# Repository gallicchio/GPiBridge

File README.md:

# GPiBridge

*By Jason Gallicchio <jason@hmc.edu> and Claude. GPIB with a lowercase i, for the Pi.
Home: [github.com/gallicchio/GPiBridge](https://github.com/gallicchio/GPiBridge).*

**How it was made:** Jason and Claude designed it in a Claude Code conversation, recorded
prompt by prompt in **[CLAUDE_CODE_CHAT.md](CLAUDE_CODE_CHAT.md)**. Claude wrote the
generators that draw the schematic, the board and the housing, the firmware and these
documents; [CLAUDE_PCB.md](CLAUDE_PCB.md) holds the lessons from earlier boards that it
followed.

**An open USB-C to GPIB (IEEE-488) adapter.** It plugs straight into an instrument's
GPIB socket, in a housing the size of a GPIB cable's hood. To the computer it is a
**Prologix-compatible controller**: one USB serial port that speaks the publicly
documented "++" commands, with the drivers built into Linux, macOS and Windows 10/11.
PyVISA-py's Prologix support (`PRLGX-ASRL0::<port>::INTFC`), EZGPIB, KE5FX's tools,
`lab-instrument-control` and scripts written for the Prologix work unchanged, given the
new port name (`HANDBOOK.md` §2). A standard **USB test-and-measurement** (USBTMC/USB488)
personality is planned for a later firmware.

| | |
|---|---|
|  |  |

Inside:
- An **RP2354A** (RP2350 with 2 MB of flash in the package). It runs the bus and USB,
  and takes new firmware over the same USB cable: `picotool` reboots it into its ROM
  bootloader from software, so nobody presses a button.
- **Real IEEE-488 transceivers**, TI's SN75160B (data) and SN75161B (control). They give
  48 mA sinks, the bus terminations and receiver hysteresis, and no load on the bus when
  unpowered. Their 5 V is switched on only after the firmware has every line released
  and the USB host has agreed to the current, so plugging the adapter into a live bus
  cannot disturb it.
- One USB-C receptacle out of the end of a thin board, three LEDs (USB, BUS, ERR), a
  BOOT button behind a pinhole, and two Raspberry Pi debug connectors (SWD and a UART
  console) under openings in the lid.
- **Its own logic analyser.** The RP2354A's second core can record all 16 bus lines
  during a transaction, at 83 ns resolution. The record goes out as a VCD, which
  PulseView decodes as GPIB (`++t capture`).

## GPiBridge Lite

The same adapter without the transceivers, for one instrument (or a few on a short
cable). Its RP2354A's pins meet the bus through 100 R each and drive it open-drain:
low to assert, let go to release, with the pads' output forced low in hardware so no
pin can ever drive a line high. It is the same size, fits the same housing (its own
lid says "Lite"), and runs the same firmware image, which reads which board it is on
at start-up (R21 on DC: 10 k up on GPiBridge, 1 k down on the Lite).

| | GPiBridge | GPiBridge Lite |
|---|---|---|
| bus drivers | SN75160B + SN75161B: 48 mA sinks, terminations, hysteresis | the RP2354A's pins, through 100 R: 12 mA sinks |
| instruments | a full bus | one, or a few on a short cable |
| unpowered (USB unplugged) | no load on the bus (TI's transceivers) | nearly none: the RP2350's pins tolerate 3.63 V unpowered; a standard bus idles at about 3.4 V |
| USB current | up to 270 mA with the drivers active | about 40 mA |
| 5 bare boards, 2 assembled (JLCPCB's quote, 2026-10-06) | $24.80 + $60.56 assembly = $85 | $25.85 + $40.18 assembly = $66 |

`DESIGN_NOTES.md` §7 has the Lite's design and its limits.

**Status: rev A of both boards has been ordered from JLCPCB, assembled, but not yet
received** (2026-10-06: 5 boards of each, 2 of them assembled). Both pass every check
(schematic ERC 0, DRC 0 at every severity with schematic parity); their JLCPCB releases
are in `mfg/release/` and `mfg/release-lite/`, and the housing (one base, a lid for each)
in `enclosure/out/`. The firmware builds and passes its host tests against a simulated
instrument, for both boards' pin layers, and sigrok's own IEEE-488 decoder reads their
simulated bus traffic correctly. Nothing has run on real hardware yet. After the order
JLCPCB ran out of L1 (the Abracon AOTA inductor) and rev A is built with a TDK
VLS201612HBX-3R3M-1 instead, chosen on 2026-10-18 in their Replace Parts dialog; the design
keeps the AOTA (`DESIGN_NOTES.md` risk 8). `BRINGUP.md` is
the plan for the first boards, and the shopping list.

## Using it

```sh
python3 tools/gpibridge.py list            # find it: its "GPiBridge GPIB" port
python3 tools/gpibridge.py idn 10          # *IDN? of the instrument at GPIB address 10
python3 tools/gpibridge.py capture 10 "*IDN?" idn    # the same, with the bus recorded: idn.vcd
```

or any Prologix program, on the "GPiBridge GPIB" port:

```
++addr 10
*IDN?
++read eoi
HEWLETT-PACKARD,33120A,0,7.0-5.0-1.0
```

The commands are the Prologix manual's (controller mode), plus `++t …` extensions
(`++t help`). `docs/PINOUT.md` has the pinout; `HANDBOOK.md` covers use, firmware
updates and recovery.

## The repository

| path | what |
|---|---|
| `PLAN.md` | the decisions and the state of the work |
| `HANDBOOK.md` | bring-up of one board, use on each OS, Prologix compatibility, recovery |
| `BRINGUP.md` | the first boards: what to buy, what plugs where, the test stages, logic analysers |
| `AGENTS.md` | how an LLM (or a person) builds, flashes, tests and debugs it |
| `DESIGN_NOTES.md` | why the design is as it is, and how rev A could fail |
| `gen/` | the generators: parts, symbols, schematic, placement, routing, silkscreen |
| `hardware/` | the KiCad 10 projects they write: `GPiBridge` and `GPiBridgeLite` (schematic, board), one library |
| `mfg/` | the JLCPCB releases (`release/`, `release-lite/`) and their checks |
| `enclosure/` | the two-part housing (FreeCAD Python) for JLC3DP: one base, a lid for each board |
| `firmware/` | Pico SDK + TinyUSB firmware, host tests with a simulated bus |
| `tools/` | checks, renders, the host tool `gpibridge.py` |
| `docs/` | pictures, pinout, schematic PDF |
| [`CLAUDE_CODE_CHAT.md`](CLAUDE_CODE_CHAT.md) | the conversation that designed it, every prompt and response |
| [`CLAUDE_PCB.md`](CLAUDE_PCB.md) | the lessons from earlier boards that it follows (a public snapshot; the working copy is in Jason's private OpticsPCBs repository) |

`python3 build.py` makes everything from the generators, for both boards
(`GPIBRIDGE_VARIANT=lite` selects the Lite in any single generator). Everything a
reviewer or a fab needs is committed, so nothing has to be built to look at the design or
order it.

## Licence

Hardware: CERN-OHL-P-2.0. Software and firmware: MIT. See `LICENSE`. Raspberry Pi's
RP2350 regulator layout and footprints (`gen/rpi_minimal/`) are theirs, MIT licensed.

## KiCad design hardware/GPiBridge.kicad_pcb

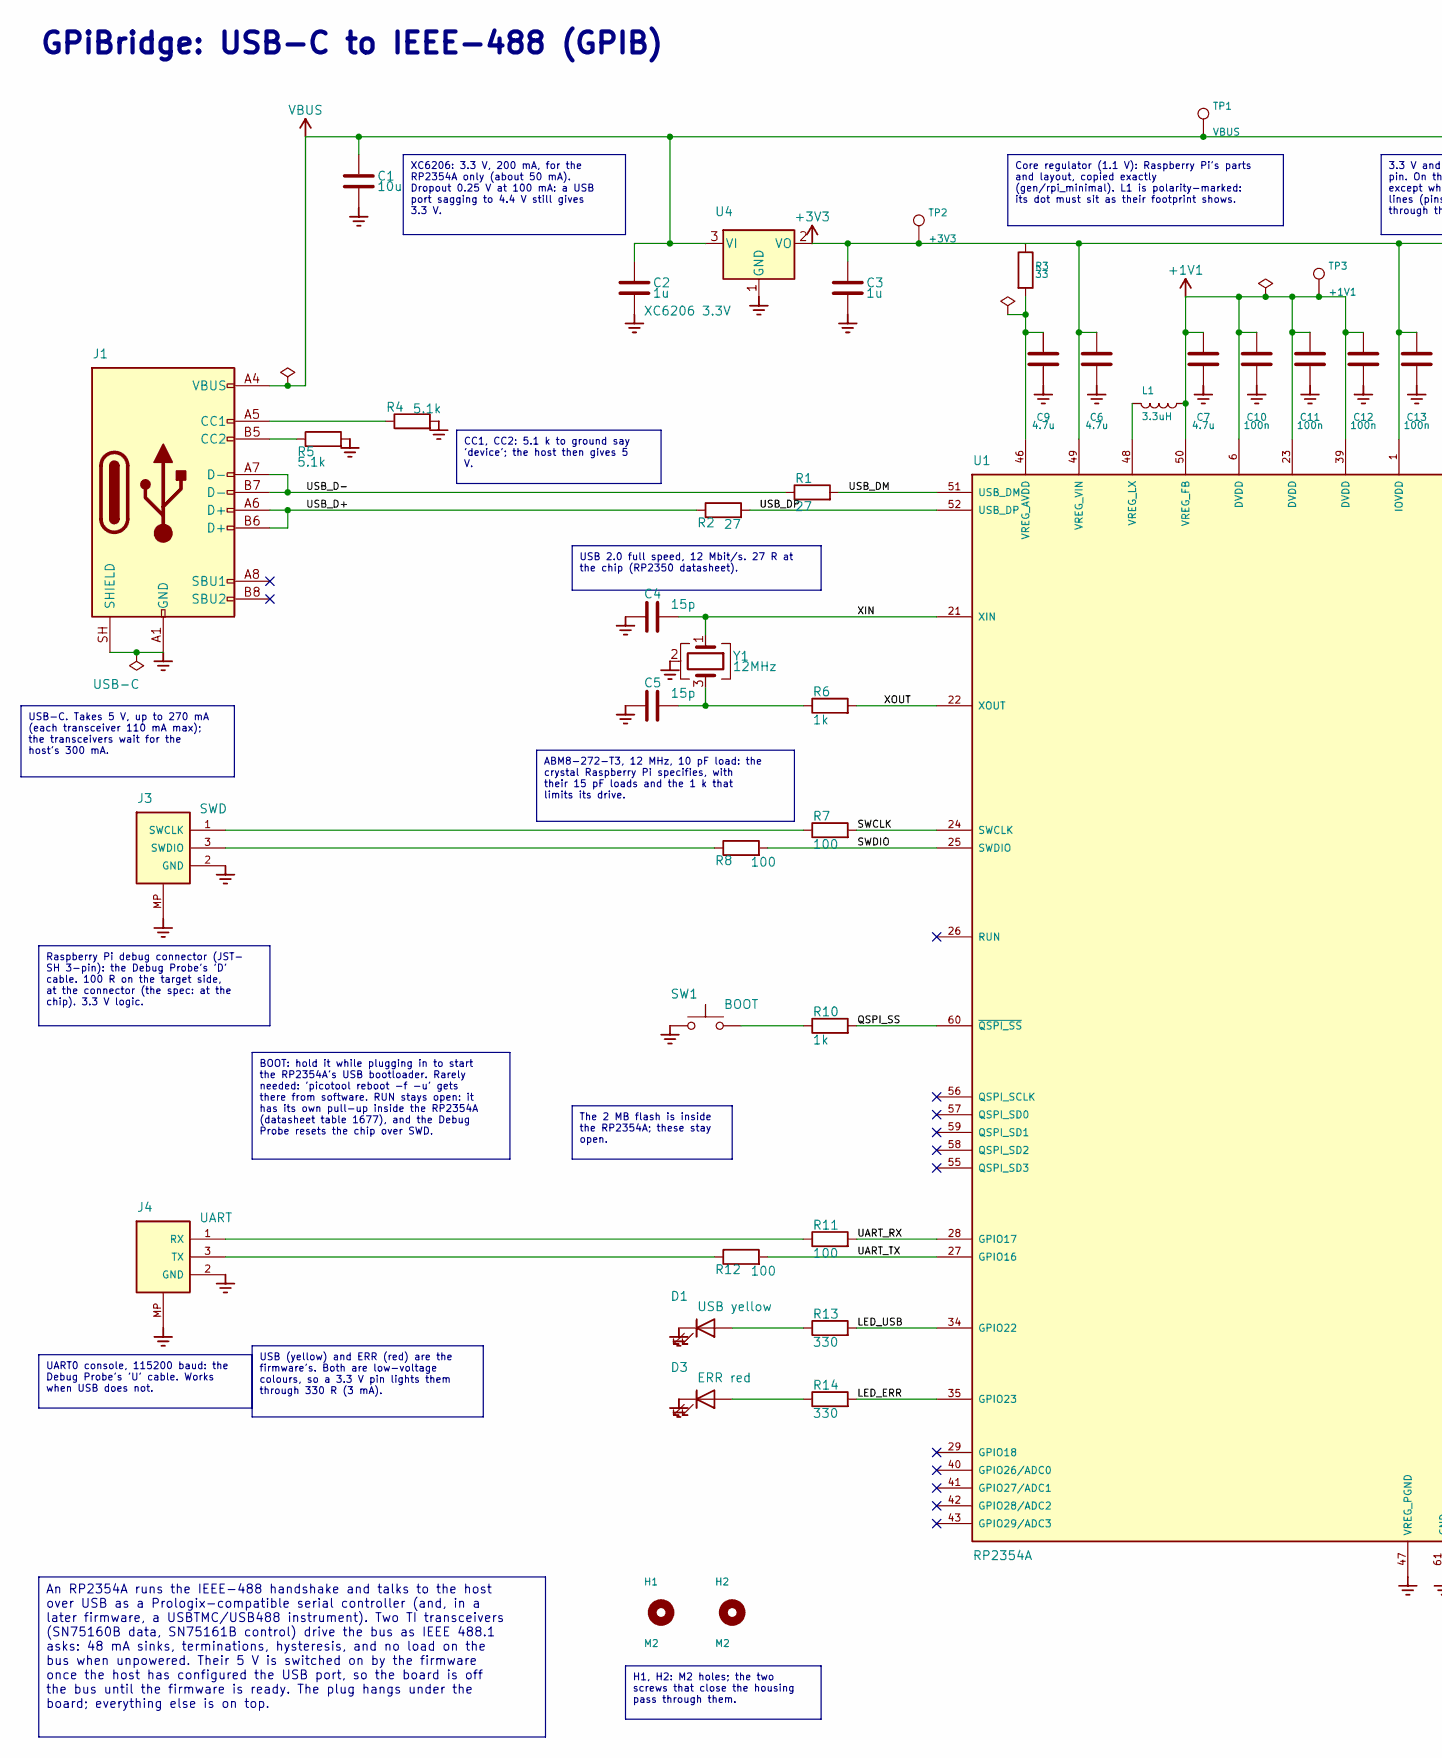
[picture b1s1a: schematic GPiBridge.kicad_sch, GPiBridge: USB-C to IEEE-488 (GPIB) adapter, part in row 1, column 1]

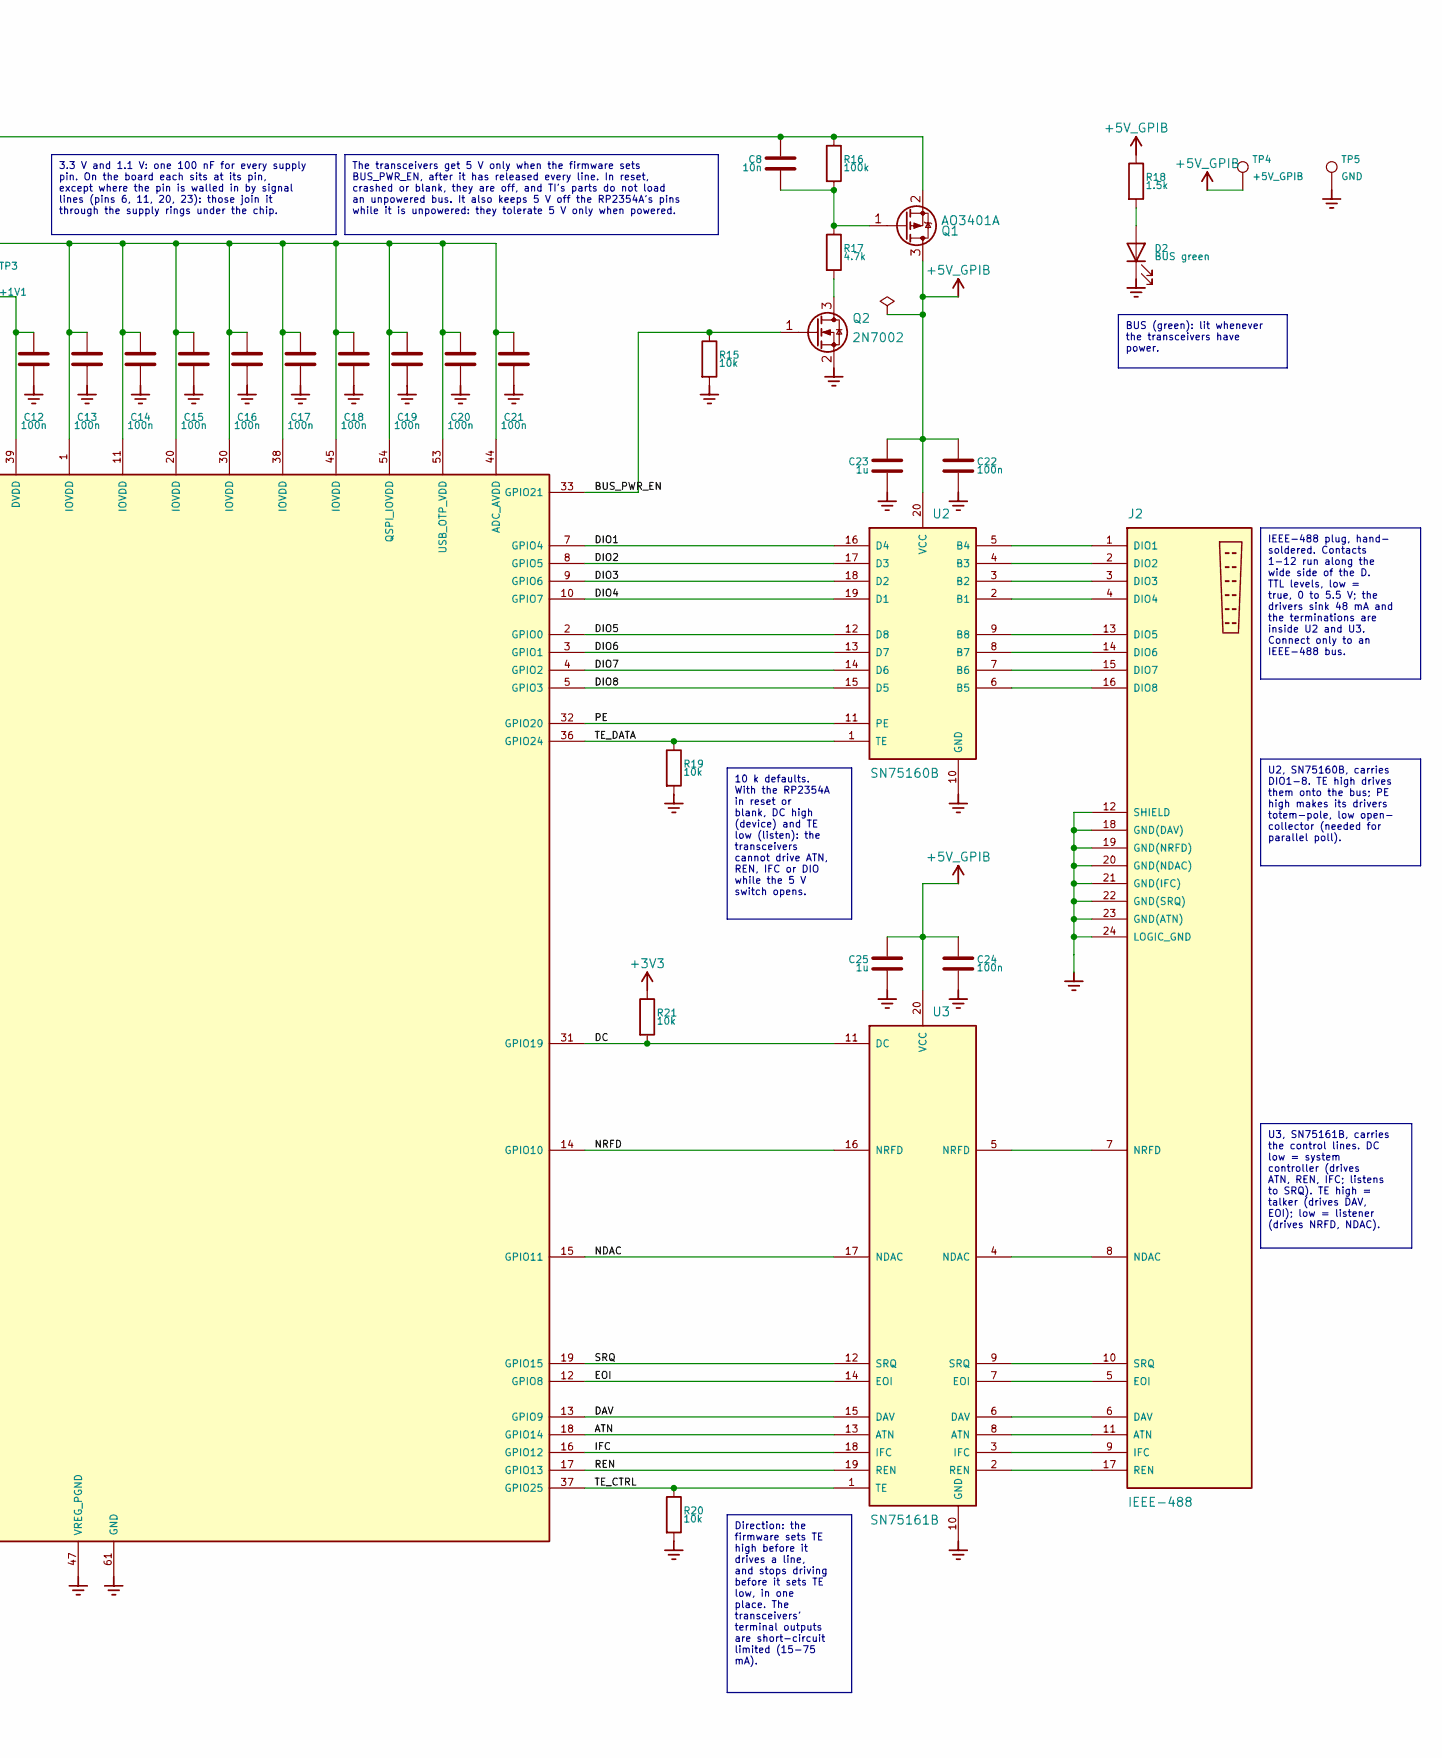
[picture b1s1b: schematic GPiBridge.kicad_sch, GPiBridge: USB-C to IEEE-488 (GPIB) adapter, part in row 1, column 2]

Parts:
C1: 10u; C_0603_1608Metric; MPN CL10A106KP8NNNC; LCSC C19702
C2, C3, C23, C25: 1u; C_0402_1005Metric; MPN CL05A105KA5NQNC; LCSC C52923
C4, C5: 15p; C_0402_1005Metric; MPN 0402CG150J500NT; LCSC C1548
C6, C7: 4.7u; C_0402_RPi_wide; MPN CL05A475MP5NRNC; LCSC C23733
C8: 10n; C_0402_1005Metric; MPN CL05B103KB5NNNC; LCSC C15195
C9: 4.7u; C_0402_RPi; MPN CL05A475MP5NRNC; LCSC C23733
C10, C11, C12, C13, C14, C15, C16, C17, C18, C19, C20, C21, C22, C24: 100n; C_0402_1005Metric; MPN CL05B104KO5NNNC; LCSC C1525
D1: USB yellow; LED_0805_2012Metric; MPN KT-0805Y; LCSC C2296
D2: BUS green; LED_0805_2012Metric; MPN KT-0805G; LCSC C2297
D3: ERR red; LED_0805_2012Metric; MPN NCD0805R1; LCSC C84256
H1, H2: M2; MountingHole_2.2mm_M2
J1: USB-C; USB_C_Receptacle_HRO_TYPE-C-31-M-12; MPN TYPE-C-31-M-12; LCSC C165948
J2: IEEE-488; IEEE488_Plug_24P_P2.16mm_DIP_Solder; MPN NorComp 111-024-113L001, or any 24-pin 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
J3: SWD; JST_SH_BM03B-SRSS-TB_1x03-1MP_P1.00mm_Vertical; MPN BM03B-SRSS-TB(LF)(SN); LCSC C160389
J4: UART; JST_SH_BM03B-SRSS-TB_1x03-1MP_P1.00mm_Vertical; MPN BM03B-SRSS-TB(LF)(SN); LCSC C160389
L1: 3.3uH; L_Abracon_AOTA-B201610_RPi; MPN AOTA-B201610S3R3-101-T; LCSC C42411119
Q1: AO3401A; SOT-23; MPN AO3401A; LCSC C15127
Q2: 2N7002; SOT-23; MPN 2N7002; LCSC C8545
R1, R2: 27; R_0402_1005Metric; MPN 0402WGF270JTCE; LCSC C25100
R3: 33; R_0402_RPi; MPN 0402WGF330JTCE; LCSC C25105
R4, R5: 5.1k; R_0402_1005Metric; MPN 0402WGF5101TCE; LCSC C25905
R6, R10: 1k; R_0402_1005Metric; MPN 0402WGF1001TCE; LCSC C11702
R7, R8, R11, R12: 100; R_0402_1005Metric; MPN 0402WGF1000TCE; LCSC C25076
R13, R14: 330; R_0402_1005Metric; MPN 0402WGF3300TCE; LCSC C25104
R15, R19, R20, R21: 10k; R_0402_1005Metric; MPN 0402WGF1002TCE; LCSC C25744
R16: 100k; R_0402_1005Metric; MPN 0402WGF1003TCE; LCSC C25741
R17: 4.7k; R_0402_1005Metric; MPN 0402WGF4701TCE; LCSC C25900
R18: 1.5k; R_0402_1005Metric; MPN 0402WGF1501TCE; LCSC C25867
SW1: BOOT; SW_SPST_TS-1088-xR020; MPN TS-1088-AR02016; LCSC C720477
TP1: VBUS; TestPoint_Pad_D1.0mm
TP2: +3V3; TestPoint_Pad_D1.0mm
TP3: +1V1; TestPoint_Pad_D1.0mm
TP4: +5V_GPIB; TestPoint_Pad_D1.0mm
TP5: GND; TestPoint_Pad_D1.0mm
U1: RP2354A; RP2350A_QFN-60_7x7mm_P0.4mm_RPi; MPN RP2354A; LCSC C41378174
U2: SN75160B; SOIC-20W_7.5x12.8mm_P1.27mm; MPN SN75160BDWR; LCSC C882412
U3: SN75161B; SOIC-20W_7.5x12.8mm_P1.27mm; MPN SN75161BDWR; LCSC C2671348
U4: XC6206 3.3V; SOT-23-3; MPN XC6206P332MR-G; LCSC C5446
Y1: 12MHz; Crystal_SMD_3225-4Pin_3.2x2.5mm; MPN ABM8-272-T3; LCSC C20625731

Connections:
+1V1: C7.1, C10.1, C11.1, C12.1, L1.1, TP3.1, U1.6 (DVDD), U1.23 (DVDD), U1.39 (DVDD), U1.50 (VREG_FB)
+3V3: C3.1, C6.1, C13.1, C14.1, C15.1, C16.1, C17.1, C18.1, C19.1, C20.1, C21.1, R3.1, R21.1, TP2.1, U1.1 (IOVDD), U1.11 (IOVDD), U1.20 (IOVDD), U1.30 (IOVDD), U1.38 (IOVDD), U1.44 (ADC_AVDD), U1.45 (IOVDD), U1.49 (VREG_VIN), U1.53 (USB_OTP_VDD), U1.54 (QSPI_IOVDD), U4.2 (VO)
+5V_GPIB: C22.1, C23.1, C24.1, C25.1, Q1.3 (D), R18.1, TP4.1, U2.20 (VCC), U3.20 (VCC)
/ATN: U1.18 (GPIO14), U3.13 (ATN)
/BUS_PWR_EN: Q2.1 (G), R15.1, U1.33 (GPIO21)
/DAV: U1.13 (GPIO9), U3.15 (DAV)
/DC: R21.2, U1.31 (GPIO19), U3.11 (DC)
/DIO1: U1.7 (GPIO4), U2.16 (D4)
/DIO2: U1.8 (GPIO5), U2.17 (D3)
/DIO3: U1.9 (GPIO6), U2.18 (D2)
/DIO4: U1.10 (GPIO7), U2.19 (D1)
/DIO5: U1.2 (GPIO0), U2.12 (D8)
/DIO6: U1.3 (GPIO1), U2.13 (D7)
/DIO7: U1.4 (GPIO2), U2.14 (D6)
/DIO8: U1.5 (GPIO3), U2.15 (D5)
/EOI: U1.12 (GPIO8), U3.14 (EOI)
/IFC: U1.16 (GPIO12), U3.18 (IFC)
/LED_ERR: R14.2, U1.35 (GPIO23)
/LED_USB: R13.2, U1.34 (GPIO22)
/NDAC: U1.15 (GPIO11), U3.17 (NDAC)
/NRFD: U1.14 (GPIO10), U3.16 (NRFD)
/PE: U1.32 (GPIO20), U2.11 (PE)
/QSPI_SS: R10.2, U1.60 (~QSPI_SS)
/REN: U1.17 (GPIO13), U3.19 (REN)
/SRQ: U1.19 (GPIO15), U3.12 (SRQ)
/SWCLK: R7.2, U1.24 (SWCLK)
/SWDIO: R8.2, U1.25 (SWDIO)
/TE_CTRL: R20.1, U1.37 (GPIO25), U3.1 (TE)
/TE_DATA: R19.1, U1.36 (GPIO24), U2.1 (TE)
/UART_RX: R11.2, U1.28 (GPIO17)
/UART_TX: R12.2, U1.27 (GPIO16)
/USB_D+: J1.A6 (D+), J1.B6 (D+), R2.1
/USB_D-: J1.A7 (D-), J1.B7 (D-), R1.1
/USB_DM: R1.2, U1.51 (USB_DM)
/USB_DP: R2.2, U1.52 (USB_DP)
/XIN: C4.2, U1.21 (XIN), Y1.1
/XOUT: R6.2, U1.22 (XOUT)
GND: C1.2, C2.2, C3.2, C4.1, C5.1, C6.2, C7.2, C9.2, C10.2, C11.2, C12.2, C13.2, C14.2, C15.2, C16.2, C17.2, C18.2, C19.2, C20.2, C21.2, C22.2, C23.2, C24.2, C25.2, D1.1 (K), D2.1 (K), D3.1 (K), J1.A1 (GND), J1.A12 (GND), J1.B1 (GND), J1.B12 (GND), J1.SH (SHIELD), J2.12 (SHIELD), J2.18 (GND(DAV)), J2.19 (GND(NRFD)), J2.20 (GND(NDAC)), J2.21 (GND(IFC)), J2.22 (GND(SRQ)), J2.23 (GND(ATN)), J2.24 (LOGIC_GND), J3.2 (GND), J3.MP, J4.2 (GND), J4.MP, Q2.2 (S), R4.2, R5.2, R15.2, R19.2, R20.2, SW1.1, TP5.1, U1.47 (VREG_PGND), U1.61 (GND), U2.10 (GND), U3.10 (GND), U4.1 (GND), Y1.2 (G), Y1.4 (G)
unnamed: C5.2, R6.1, Y1.3
unnamed: D1.2 (A), R13.1
unnamed: D2.2 (A), R18.2
unnamed: D3.2 (A), R14.1
unnamed: J1.A5 (CC1), R4.1
unnamed: J1.B5 (CC2), R5.1
unnamed: J2.11 (ATN), U3.8 (ATN)
unnamed: J2.6 (DAV), U3.6 (DAV)
unnamed: J2.1 (DIO1), U2.5 (B4)
unnamed: J2.2 (DIO2), U2.4 (B3)
unnamed: J2.3 (DIO3), U2.3 (B2)
unnamed: J2.4 (DIO4), U2.2 (B1)
unnamed: J2.13 (DIO5), U2.9 (B8)
unnamed: J2.14 (DIO6), U2.8 (B7)
unnamed: J2.15 (DIO7), U2.7 (B6)
unnamed: J2.16 (DIO8), U2.6 (B5)
unnamed: J2.5 (EOI), U3.7 (EOI)
unnamed: J2.9 (IFC), U3.3 (IFC)
unnamed: J2.8 (NDAC), U3.4 (NDAC)
unnamed: J2.7 (NRFD), U3.5 (NRFD)
unnamed: J2.17 (REN), U3.2 (REN)
unnamed: J2.10 (SRQ), U3.9 (SRQ)
unnamed: J3.1 (SWCLK), R7.1
unnamed: J3.3 (SWDIO), R8.1
unnamed: J4.1 (RX), R11.1
unnamed: J4.3 (TX), R12.1
unnamed: C8.2, Q1.1 (G), R16.2, R17.1
unnamed: Q2.3 (D), R17.2
unnamed: R10.1, SW1.2
unnamed: C9.1, R3.2, U1.46 (VREG_AVDD)
unnamed: L1.2, U1.48 (VREG_LX)
VBUS: C1.1, C2.1, C8.1, J1.A4 (VBUS), J1.A9 (VBUS), J1.B4 (VBUS), J1.B9 (VBUS), Q1.2 (S), R16.1, TP1.1, U4.3 (VI)

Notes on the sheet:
GPiBridge: USB-C to IEEE-488 (GPIB)
The transceivers get 5 V only when the firmware sets BUS_PWR_EN, after it has released every line. In reset, crashed or blank, they are off, and TI's parts do not load an unpowered bus. It also keeps 5 V off the RP2354A's pins while it is unpowered: they tolerate 5 V only when powered.
H1, H2: M2 holes; the two screws that close the housing pass through them.
USB-C. Takes 5 V, up to 270 mA (each transceiver 110 mA max); the transceivers wait for the host's 300 mA.
ABM8-272-T3, 12 MHz, 10 pF load: the crystal Raspberry Pi specifies, with their 15 pF loads and the 1 k that limits its drive.
The 2 MB flash is inside the RP2354A; these stay open.
CC1, CC2: 5.1 k to ground say 'device'; the host then gives 5 V.
IEEE-488 plug, hand- soldered. Contacts 1-12 run along the wide side of the D. TTL levels, low = true, 0 to 5.5 V; the drivers sink 48 mA and the terminations are inside U2 and U3. Connect only to an IEEE-488 bus.
An RP2354A runs the IEEE-488 handshake and talks to the host over USB as a Prologix-compatible serial controller (and, in a later firmware, a USBTMC/USB488 instrument). Two TI transceivers (SN75160B data, SN75161B control) drive the bus as IEEE 488.1 asks: 48 mA sinks, terminations, hysteresis, and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
BUS (green): lit whenever the transceivers have power.
10 k defaults. With the RP2354A in reset or blank, DC high (device) and TE low (listen): the transceivers cannot drive ATN, REN, IFC or DIO while the 5 V switch opens.
Core regulator (1.1 V): Raspberry Pi's parts and layout, copied exactly (gen/rpi_minimal). L1 is polarity-marked: its dot must sit as their footprint shows.
U2, SN75160B, carries DIO1-8. TE high drives them onto the bus; PE high makes its drivers totem-pole, low open- collector (needed for parallel poll).
USB (yellow) and ERR (red) are the firmware's. Both are low-voltage colours, so a 3.3 V pin lights them through 330 R (3 mA).
3.3 V and 1.1 V: one 100 nF for every supply pin. On the board each sits at its pin, except where the pin is walled in by signal lines (pins 6, 11, 20, 23): those join it through the supply rings under the chip.
USB 2.0 full speed, 12 Mbit/s. 27 R at the chip (RP2350 datasheet).
XC6206: 3.3 V, 200 mA, for the RP2354A only (about 50 mA). Dropout 0.25 V at 100 mA: a USB port sagging to 4.4 V still gives 3.3 V.
Direction: the firmware sets TE high before it drives a line, and stops driving before it sets TE low, in one place. The transceivers' terminal outputs are short-circuit limited (15-75 mA).
UART0 console, 115200 baud: the Debug Probe's 'U' cable. Works when USB does not.
BOOT: hold it while plugging in to start the RP2354A's USB bootloader. Rarely needed: 'picotool reboot -f -u' gets there from software. RUN stays open: it has its own pull-up inside the RP2354A (datasheet table 1677), and the Debug Probe resets the chip over SWD.
U3, SN75161B, carries the control lines. DC low = system controller (drives ATN, REN, IFC; listens to SRQ). TE high = talker (drives DAV, EOI); low = listener (drives NRFD, NDAC).
Raspberry Pi debug connector (JST- SH 3-pin): the Debug Probe's 'D' cable. 100 R on the target side, at the connector (the spec: at the chip). 3.3 V logic.

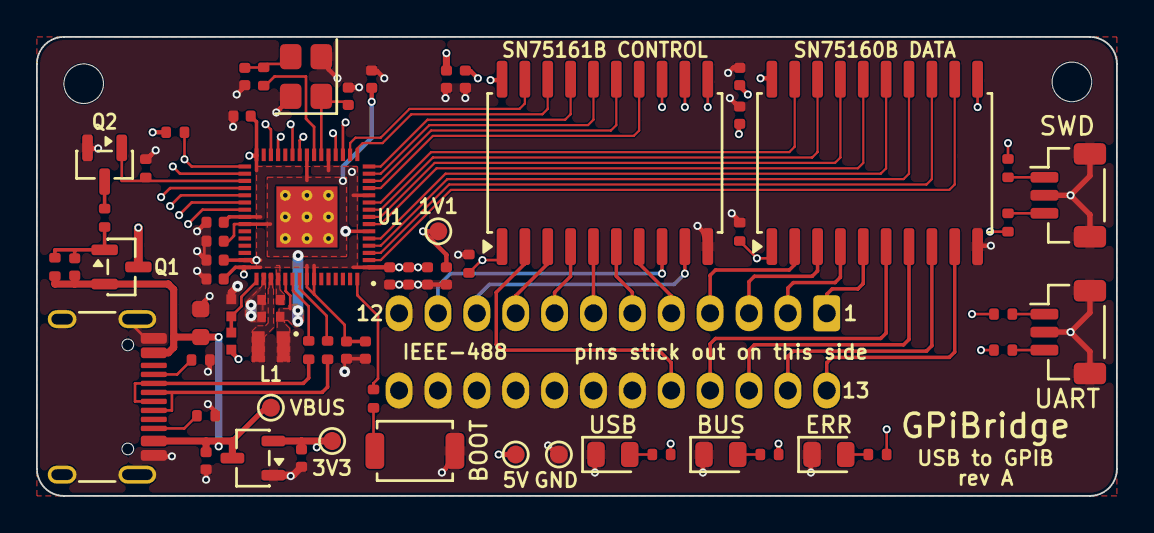
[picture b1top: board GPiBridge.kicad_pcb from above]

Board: 4 copper layers, 60.0 x 25.5 mm, 68 parts (1 on the bottom side), 70 nets.

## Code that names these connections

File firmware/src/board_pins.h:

/* board_pins.h: which RP2354A GPIO does what on GPiBridge and GPiBridge Lite rev A.
 * WRITTEN BY gen/firmware_pins.py FROM gen/pins.py: edit that, not this. */
#pragma once

/* The data byte: GPIO 0-7, nibbles swapped (GPIO0-3 carry DIO5-8, GPIO4-7 carry
 * DIO1-4) so that the sixteen data wires cross nowhere on the board.  bus_byte()
 * and wire_byte() convert. */
#define PIN_DATA_BASE   0
#define PIN_DIO1        4
#define PIN_DIO2        5
#define PIN_DIO3        6
#define PIN_DIO4        7
#define PIN_DIO5        0
#define PIN_DIO6        1
#define PIN_DIO7        2
#define PIN_DIO8        3

#define PIN_EOI          8   /* end or identify, via SN75161B */
#define PIN_DAV          9   /* data valid */
#define PIN_NRFD         10   /* not ready for data */
#define PIN_NDAC         11   /* not data accepted */
#define PIN_IFC          12   /* interface clear */
#define PIN_REN          13   /* remote enable */
#define PIN_ATN          14   /* attention */
#define PIN_SRQ          15   /* service request */

#define PIN_TE_DATA      24   /* SN75160B talk enable: high drives DIO onto the bus */
#define PIN_TE_CTRL      25   /* SN75161B talk enable */
#define PIN_DC           19   /* SN75161B direction: low = controller (drives ATN, REN, IFC); also the board ID: 10 k up on GPiBridge, 1 k down on GPiBridge Lite */
#define PIN_PE           20   /* SN75160B pull-up enable: high = totem-pole DIO, low = open collector */
#define PIN_BUS_PWR_EN   21   /* high switches 5 V to the transceivers */
#define PIN_LED_USB      22   /* yellow LED, high = on */
#define PIN_LED_ERR      23   /* red LED, high = on */
#define PIN_UART_TX      16   /* UART0 TX, to the debug connector */
#define PIN_UART_RX      17   /* UART0 RX, from the debug connector */

/* the bus lines' pins, for setting them up together */
#define BUS_PIN_MASK    ((0xffu << PIN_DATA_BASE) | (1u << PIN_EOI) | (1u << PIN_DAV) | (1u << PIN_NRFD) | \
                         (1u << PIN_NDAC) | (1u << PIN_IFC) | (1u << PIN_REN) | (1u << PIN_ATN) | \
                         (1u << PIN_SRQ))

/* the board's 10 k resistors, which hold these pins while the RP2354A is in reset */
#define BOARD_PULL_UP_MASK    ((1u << PIN_DC))
#define BOARD_PULL_DOWN_MASK  ((1u << PIN_TE_DATA) | (1u << PIN_TE_CTRL) | (1u << PIN_BUS_PWR_EN))

/* the data byte as the bus carries it (DIO1 = bit 0) <-> as GPIO 0-7 carry it */
static inline unsigned wire_byte(unsigned b) { return ((b << 4) | (b >> 4)) & 0xffu; }
static inline unsigned bus_byte(unsigned w) { return ((w << 4) | (w >> 4)) & 0xffu; }

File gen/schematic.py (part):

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    xRs = xR + 20.32                        # the series resistors' column
    hhJ = len(SYMB.PLUG_LEFT) * G / 2 + G / 2
    J2x = xR + 48.26
    J2y = ry(gpin("DIO1")) + hhJ - G
    J2 = part("GPIB", "J2", J2x, J2y, ref_at=(J2x - 8.89, J2y - hhJ - 1.0), val_at=(J2x - 8.89, J2y + hhJ + 1.2))
    for p in SYMB.PLUG_LEFT:
        if not p or p[2] == "passive":
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    note(J2x + 10.5, y - 14.0, "DC: the board ID. R21 is 1 k down here, 10 k up on GPiBridge. The firmware "
         "reads DC at start-up, before it drives anything: low runs the Lite's pin layer.", cols=22)
    # the green BUS LED, on the signal that powers GPiBridge's transceivers
    y = ry(gpin("BUS_PWR_EN"))
    l, r = hpart("R100", "R18", xR + 15.24, y)
    W(pin(gpin("BUS_PWR_EN")), l)
    label(xR + 0.8, y, "BUS_PWR_EN")
    xd = xR + 27.94
    d2 = part("LED_G", "D2", xd, y, rot=180, value="BUS green", ref_at=(xd - 5.6, y - 4.8), val_at=(xd - 2.2, y - 4.8))
    W(r, d2.pin("2"))
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    part("TP", "TP5", xt5, YV + 7.62, value="GND", ref_at=(xt5 + 1.5, YV + 4.0), val_at=(xt5 + 1.5, YV + 5.7),
         fsize=1.0)
    gnd(xt5, YV + 7.62)
    note(xR + 3.0, ry(gpin("TE_DATA")) + 3.0,
         "R30-R45: 100 R in every line (R30 + the GPIO number). They hold the current to about 35 mA if an "
         "instrument drives a line high while the RP2354A holds it low, and static on a contact reaches the "
         "pin through them. A line held low sits at about 0.25 V with one instrument's terminations on it "
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    note(J2x + 10.5, J2y - hhJ, "IEEE-488 plug, hand-soldered. Contacts 1-12 run along the wide side of the D. "
         "TTL levels, low = true. The RP2354A's bus pins are 5 V tolerant while it is powered (5.5 V max) and "
         "take up to 3.63 V while it is not: a standard bus idles at about 3.4 V.", cols=22)
    note(J2x + 10.5, ry(gpin("NRFD")) - 4.0, "Open-drain: a line is asserted by driving its pin low and "
         "released by letting go. NRFD, NDAC and SRQ are wired-OR on every bus, and the Lite treats the other "
         "lines the same way, so it never needs to know who else is driving.", cols=22)

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    def ry(num):
        return pin(num)[1]

    xL, xR = pin("51")[0], pin(gpin("DIO1"))[0]

    # ---- supplies along the top: each pin's wire rises to its rail; its
    # capacitor hangs from that wire, ground just below
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    J(xst, ydm); J(xst, ydp)
    l, r = hpart("R27", "R1", xL - 17.78, ydm)
    W((xst, ydm), l); W(r, pin("51"))
    label(xst + 3.0, ydm, "USB_D-"); label(r[0] + 1.0, ydm, "USB_DM")
    l, r = hpart("R27", "R2", xL - 30.48, ydp, ref_at=(xL - 34.29, ydp + 3.0), val_at=(xL - 30.48, ydp + 1.6))
    W((xst, ydp), l); W(r, pin("52"))
    label(xst + 3.0, ydp, "USB_D+"); label(r[0] + 1.0, ydp, "USB_DP")
    note(xL - 52.0, ydp + 4.6, "USB 2.0 full speed, 12 Mbit/s. 27 R at the chip (RP2350 datasheet).", cols=40)
    cc1, cc2 = J1.pin("A5"), J1.pin("B5")
    l, r = hpart("R5K1", "R5", cc2[0] + 7.62, cc2[1], ref_at=(cc2[0] + 3.2, cc2[1] + 3.0),
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    note(xL - 52.0, ry("57") - 1.0, "The 2 MB flash is inside the RP2354A; these stay open.", cols=24)

    # ---- UART --------------------------------------------------------------------
    yrx, ytx = ry(gpin("UART_RX")), ry(gpin("UART_TX"))
    J4 = part("JSTSH3", "J4", J3x, ytx, value="UART", sym="Conn_UART", ref_at=(J3x - 3.81, ytx - 6.4),
              val_at=(J3x + 4.6, ytx - 6.4))
    l, r = hpart("R100", "R11", xL - 15.24, yrx)
    W(J4.pin("1"), l); W(r, pin(gpin("UART_RX")))
    l, r = hpart("R100", "R12", xL - 27.94, ytx, ref_at=(xL - 32.2, ytx + 3.0), val_at=(xL - 26.4, ytx + 1.6))
    W(J4.pin("3"), l); W(r, pin(gpin("UART_TX")))
    gnd(*J4.pin("2")); gnd(*J4.pin("MP"))
    note(J3x - 18.0, ytx + 14.5, "UART0 console, 115200 baud: the Debug Probe's 'U' cable. Works when USB "
         "does not.", cols=34)
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        d = part(key, dref, xL - 33.02, y, value=lab, ref_at=(xL - 38.1, y - 3.2), val_at=(xL - 34.3, y - 3.2))
        W(d.pin("2"), l)
        gnd(*d.pin("1"))
    note(xL - 98.0, ry(gpin("LED_USB")) + 3.0, "USB (yellow) and ERR (red) are the firmware's. Both are "
         "low-voltage colours, so a 3.3 V pin lights them through 330 R (3 mA).", cols=40)

    for name, num in (("XIN", "21"), ("SWCLK", "24"), ("SWDIO", "25"), ("QSPI_SS", "60"),
                      ("UART_RX", gpin("UART_RX")), ("UART_TX", gpin("UART_TX")),
                      ("LED_USB", gpin("LED_USB")), ("LED_ERR", gpin("LED_ERR"))):
        x, y = pin(num)
        label(x - 11.5, y, name)
    label(pin("22")[0] - 7.5, ry("22"), "XOUT")

    # ---- spare GPIOs ---------------------------------------------------------------
    for net in ("GP18", "GP26", "GP27", "GP28", "GP29"):
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        xp = xR + 8.89                          # the pull resistors' column, on the MCU side
        xRs = xR + 17.78                        # the series resistors' column
        hh2 = len(SYMB.SN60_LEFT) * G / 2 + G / 2
        U2y = ry(gpin("DIO1")) + hh2 - G
        U2 = part("SN75160B", "U2", U2x, U2y, ref_at=(U2x + 1.0, U2y - hh2 - 1.0), val_at=(U2x - 7.62, U2y + hh2 + 1.2))
        hh3 = len(SYMB.SN61_LEFT) * G / 2 + G / 2
        U3y = ry(gpin("DC")) + hh3 - G
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            t, b = vpart("R10K", ref, xp + 3.81, y + 3.81, fsize=1.0)
            gnd(*b)
            J(xp + 3.81, y)
        note(xRs + 2.0, ry(gpin("TE_CTRL")) + 4.0,
             "Direction: the firmware sets TE high before it drives a line, and stops driving before it "
             "sets TE low, in one place. The transceivers' terminal outputs are short-circuit limited "
             "(15-75 mA).", cols=17)
        note(xRs + 2.0, ry(gpin("TE_DATA")) + 4.0,
             "10 k defaults. With the RP2354A in reset or blank, DC high (device) and TE low (listen): "
             "the transceivers cannot drive ATN, REN, IFC or DIO while the 5 V switch opens.", cols=17)

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        gnd(*Q2.pin("2"))
        g2 = Q2.pin("1")
        xb = xR + 7.62
        W(pin(gpin("BUS_PWR_EN")), (xb, ry(gpin("BUS_PWR_EN"))), (xb, g2[1]), g2)
        label(xR + 0.8, ry(gpin("BUS_PWR_EN")), "BUS_PWR_EN")
        xpd = (xb + g2[0]) / 2
        t, b = vpart("R10K", "R15", xpd, g2[1] + 3.81, fsize=1.0)
        gnd(*b)
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        # ---- the plug ------------------------------------------------------------------
        hhJ = len(SYMB.PLUG_LEFT) * G / 2 + G / 2
        J2x = U2x + 38.1
        J2y = ry(gpin("DIO1")) + hhJ - G
        J2 = part("GPIB", "J2", J2x, J2y, ref_at=(J2x - 8.89, J2y - hhJ - 1.0), val_at=(J2x - 8.89, J2y + hhJ + 1.2))
        u2b = {p[1]: p[0] for p in SYMB.SN60_RIGHT if p}
        u3b = {p[1]: p[0] for p in SYMB.SN61_RIGHT if p}
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        note(J2x + 10.5, J2y - hhJ, "IEEE-488 plug, hand-soldered. Contacts 1-12 run along the wide side of the D. "
             "TTL levels, low = true, 0 to 5.5 V; the drivers sink 48 mA and the terminations are inside U2 and "
             "U3. Connect only to an IEEE-488 bus.", cols=22)
        note(J2x + 10.5, ry(gpin("DIO8")) + 10.0, "U2, SN75160B, carries DIO1-8. TE high drives them onto "
             "the bus; PE high makes its drivers totem-pole, low open-collector (needed for parallel poll).", cols=22)
        note(J2x + 10.5, ry(gpin("NRFD")) - 4.0, "U3, SN75161B, carries the control lines. DC low = system "
             "controller (drives ATN, REN, IFC; listens to SRQ). TE high = talker (drives DAV, EOI); low = "
             "listener (drives NRFD, NDAC).", cols=22)
    else:
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
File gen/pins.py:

"""Which RP2354A pin does what: the one source of truth.

The schematic, the MCU symbol's pin order, the firmware's pin header
(firmware/src/board_pins.h, written by gen/firmware_pins.py) and the pinout
document are all made from this file.

The bus lines are active low on the wire.  The SN7516x transceivers do not
invert, so a terminal pin is low when its bus line is asserted.  The firmware
inverts them (in C, firmware/src/hal_rp2350.c; a PIO engine would use the
pads' INOVER/OUTOVER), so the bus engine sees 1 = asserted.

PIO needs:
  * the eight data lines and EOI on consecutive pins (GPIO0-8): one `in` or
    `out` of 9 bits;
  * NRFD and NDAC consecutive (GPIO10-11): one 2-bit side-set for the listener;
  * DAV on its own pin (GPIO9): a 1-bit side-set for the talker.

The data byte sits on GPIO0-7 with its nibbles swapped: GPIO0-3 carry DIO5-8
and GPIO4-7 carry DIO1-4.  That order lets all sixteen data wires (MCU to
SN75160B, SN75160B to the plug) run on the top copper layer without one
crossing: the RP2354A's pins meet the transceiver's in that order, and the
transceiver's bus pins then meet the plug's two rows in order.  The firmware
swaps the nibbles on the way in and out (byte = (b << 4 | b >> 4) & 0xFF).
"""

# GPIO -> (net, what it is)
GPIO = {
    0: ("DIO5", "data, via SN75160B; GPIO0-3 carry DIO5-8 and GPIO4-7 DIO1-4, so no data wires cross"),
    1: ("DIO6", ""), 2: ("DIO7", ""),
    3: ("DIO8", ""), 4: ("DIO1", ""), 5: ("DIO2", ""), 6: ("DIO3", ""), 7: ("DIO4", ""),
    8: ("EOI", "end or identify, via SN75161B"), 9: ("DAV", "data valid"),
    10: ("NRFD", "not ready for data"), 11: ("NDAC", "not data accepted"),
    12: ("IFC", "interface clear"), 13: ("REN", "remote enable"), 14: ("ATN", "attention"),
    15: ("SRQ", "service request"),
    16: ("UART_TX", "UART0 TX, to the debug connector"), 17: ("UART_RX", "UART0 RX, from the debug connector"),
    18: ("GP18", "spare"),
    19: ("DC", "SN75161B direction: low = controller (drives ATN, REN, IFC); also the board ID: "
               "10 k up on GPiBridge, 1 k down on GPiBridge Lite"),
    20: ("PE", "SN75160B pull-up enable: high = totem-pole DIO, low = open collector"),
    21: ("BUS_PWR_EN", "high switches 5 V to the transceivers"),
    22: ("LED_USB", "yellow LED, high = on"), 23: ("LED_ERR", "red LED, high = on"),
    24: ("TE_DATA", "SN75160B talk enable: high drives DIO onto the bus"),
    25: ("TE_CTRL", "SN75161B talk enable"),
    26: ("GP26", "spare"), 27: ("GP27", "spare"), 28: ("GP28", "spare"), 29: ("GP29", "spare"),
}

NET = {g: n for g, (n, _) in GPIO.items()}
GPIO_OF = {n: g for g, n in NET.items()}

# The order of the MCU symbol's right side, top to bottom (None = an empty
# row).  It is the order of the transceivers' rows, so every bus line runs
# straight across the sheet.  Lines with a pull-up get five empty rows above
# them, room for the resistor and its 3.3 V flag to hang from their own line
# without crossing another; DC, first, has the gap above U3.
GAP_U2_U3 = 16         # rows between the two transceivers: U2's GND, U3's VCC, notes
RIGHT_ROWS = (["BUS_PWR_EN", None, None]
              + ["DIO1", "DIO2", "DIO3", "DIO4", None, "DIO5", "DIO6", "DIO7", "DIO8"] + [None, "PE", "TE_DATA"]
              + [None] * GAP_U2_U3
              + ["DC"] + [None] * 5 + ["NRFD"] + [None] * 5 + ["NDAC"] + [None] * 5
              + ["SRQ", "EOI", None, "DAV", "ATN", "IFC", "REN", "TE_CTRL"])
# The 10 k pulls that set the transceivers' state while the RP2354A is in
# reset or blank.  (No series resistors: the transceivers' terminal outputs
# are short-circuit limited, and the firmware changes direction in one
# place, TE before the pins when talking, the pins before TE when listening.)
PULL_R = {"DC": "R21", "TE_DATA": "R19", "TE_CTRL": "R20", "BUS_PWR_EN": "R15"}

# Which of the SN75160B's eight identical channels carries each data line
# (channel c: bus pin Bc = pin c + 1, terminal pin Dc = pin 20 - c).  The
# channels are interchangeable, so they are assigned to suit the board.  U2
# lies above contacts 1-4 (upper row) and 13-16 (lower row), its bus pins
# B1..B8 left to right: B1-B4 run straight down to contacts 4, 3, 2, 1, and
# B5-B8 pass right of contact 1 into the gap between the rows and on to
# contacts 16, 15, 14, 13, all on the top layer.  The terminal pins D1..D8
# then read DIO4, 3, 2, 1, 8, 7, 6, 5, the order of GPIO7..GPIO0 as they
# leave the RP2354A.
U2_CHANNEL = {"DIO1": 4, "DIO2": 3, "DIO3": 2, "DIO4": 1, "DIO5": 8, "DIO6": 7, "DIO7": 6, "DIO8": 5}
# The left side, top to bottom: fixed-function pins by name, GPIOs by net.
LEFT_ROWS = (["USB_DM", "USB_DP"] + [None] * 5
             + ["XIN"] + [None] * 4 + ["XOUT"] + [None] * 6
             + ["SWCLK", "SWDIO"] + [None] * 4
             + ["RUN"] + [None] * 4 + ["QSPI_SS"] + [None] * 3
             + ["QSPI_SCLK", "QSPI_SD0", "QSPI_SD1", "QSPI_SD2", "QSPI_SD3"] + [None] * 3
             + ["UART_RX", "UART_TX"] + [None] * 3
             + ["LED_USB"] + [None] * 3 + ["LED_ERR"] + [None] * 2
             + ["GP18", "GP26", "GP27", "GP28", "GP29"])

# Only DC needs a pull-up.  After an RP2354A reset its pins pull down, and
# the 5 V switch takes about 1 ms to open; DC high in that time keeps the
# SN75161B a device, so it can never drive ATN, REN or IFC (an IFC that long
# would reset every instrument's interface).  NRFD, NDAC and SRQ may assert
# for that 1 ms: NRFD and NDAC only pause a handshake (the three-wire
# handshake waits for every listener), SRQ is at worst a spurious service
# request.
PULL_UP = ["DC"]                                 # 10 k to 3.3 V: device mode
PULL_DOWN = ["TE_DATA", "TE_CTRL", "BUS_PWR_EN"]  # 10 k to ground: receive, transceivers off

# GPiBridge Lite has no transceivers, so DC, PE, TE_DATA and TE_CTRL go
# nowhere, except that DC carries the board's identity: R21 is 10 k to 3.3 V
# here and 1 k to ground on the Lite, in the same place.  The firmware reads
# DC before it drives anything: high, the transceiver pin layer; low, the
# Lite's.  (A spare pin with a strap would need an escape, and GP26-29 are
# walled in by the decoupling capacitors' copper.)  BUS_PWR_EN lights the
# Lite's green BUS LED directly.
LITE_PULL_DOWN = {"DC": "R21"}                   # 1 k to ground: the Lite's board ID
LITE_UNUSED = ["PE", "TE_DATA", "TE_CTRL"]

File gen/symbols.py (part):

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# ---------------------------------------------------------------------------
# RP2354A: RP2350 datasheet, Table 1674 (QFN-60 numbers) and Figure "RP2350A
# pinout"; the same numbers as KiCad's MCU_RaspberryPi:RP2350A.  The four
# QSPI data pins and SCLK reach the flash inside the package; only QSPI_SS is
# used outside (BOOTSEL).
import pins as PINS

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# own symbol draws it as ~{PE}, which is wrong.  Terminal side left, bus right.
_T60 = {"DIO%d" % i: (str(20 - PINS.U2_CHANNEL["DIO%d" % i]), "D%d" % PINS.U2_CHANNEL["DIO%d" % i]) for i in range(1, 9)}
_T60.update({"PE": ("11", "PE"), "TE_DATA": ("1", "TE")})
U2_ROWS = PINS.RIGHT_ROWS[PINS.RIGHT_ROWS.index("DIO1"):PINS.RIGHT_ROWS.index("TE_DATA") + 1]
SN60_LEFT = [((_T60[n][0], _T60[n][1], I if n in ("PE", "TE_DATA") else B) if n else None) for n in U2_ROWS]
SN60_RIGHT = [((str(PINS.U2_CHANNEL[n] + 1), "B%d" % PINS.U2_CHANNEL[n], B) if n and n.startswith("DIO") else None)
              for n in U2_ROWS]
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                      top_x=[0.0], bottom_x=[2 * G])


# SN75161B (TI SLLS005B, DW package pin figure): 1 TE, 2 REN, 3 IFC, 4 NDAC,
# 5 NRFD, 6 DAV, 7 EOI, 8 ATN, 9 SRQ (bus side), 10 GND, 11 DC, 12 SRQ,
# 13 ATN, 14 EOI, 15 DAV, 16 NRFD, 17 NDAC, 18 IFC, 19 REN (terminal side),
# 20 VCC.  Rows in the order of the MCU's GPIO8-15, each straight across.
_T61 = {"EOI": "14", "DAV": "15", "NRFD": "16", "NDAC": "17", "ATN": "13", "SRQ": "12", "IFC": "18",
        "REN": "19", "TE_CTRL": "1", "DC": "11"}
_B61 = {"EOI": "7", "DAV": "6", "NRFD": "5", "NDAC": "4", "ATN": "8", "SRQ": "9", "IFC": "3", "REN": "2"}
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# runs straight across; the eight grounds follow
# runs straight across; the eight ground contacts sit in the gap between the
# two transceivers, where no bus line runs
_span = PINS.RIGHT_ROWS[PINS.RIGHT_ROWS.index("DIO1"):PINS.RIGHT_ROWS.index("REN") + 1]
_gap0 = _span.index("TE_DATA") + 4
PLUG_LEFT = [((str(_CONTACT[n]), n, B) if n in _CONTACT else None) for n in _span]
for _k, _c in enumerate((12, 18, 19, 20, 21, 22, 23, 24)):
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

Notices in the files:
hardware/GPiBridge.kicad_sch:
Hardware CERN-OHL-P-2.0, software MIT
parts and their libraries:
From Raspberry Pi's RP2350A Minimal design (MIT licence), so their regulator layout can be copied exactly
